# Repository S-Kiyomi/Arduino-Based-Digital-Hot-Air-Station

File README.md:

# 858d HOT AIR REWORK STATION (SVARD858d)

> *sile bace dalam bahase kamek mun kau daan ngerati inggris: [Bahasa Indonesia](/docs/README_ID.md)*

This **ATmega328P** microcontroller-based digital hot-air rework station is an open-source DIY project designed to deliver high(not or maybe)precision temperature control and airflow management. It utilizes a standard 858D hot-air handle, a K-type thermocouple sensor (MAX6675), and a rotary encoder for an intuitive user interface.

In **v2.0**, the firmware has been completely refactored from the standard Arduino core environment to **Pure AVR Bare-Metal C/C++** to achieve overhead-free execution, lightning-fast response times, and an extremely low memory footprint.

> **HIGH VOLTAGE SAFETY WARNING (220V AC)**
> 
> This project deals directly with lethal 220V/230V AC mains electricity. Incorrect assembly can lead to hardware destruction, fire hazard, or fatal electric shock.
> - Never touch any part of the TRIAC/Heater circuitry while the system is connected to mains power.
> - Ensure high-voltage circuits are physically and optocoupled-isolated from microcontroller lines.
> - Assemble and operate entirely at your own risk.
> - DO WITH YOUR OWN RISK
> - MATI TANAM

---

## Key Features

- **Pure Bare-Metal Firmware (v2.0):** Runs without Arduino library dependencies (`Wire.h`, `LiquidCrystal_I2C.h`, `EEPROM.h`, `pinMode`, `digitalWrite`). Compiled natively via `avr-gcc` and `Makefile`.
- **Extreme Memory Footprint Optimization:** Extremely lightweight footprint (~6.4 KB Flash & 128 Bytes SRAM). UI text strings are stored in Flash ROM (`PROGMEM`) with custom lightweight integer formatting.
- **Non-Volatile EEPROM Storage:** Target temperature (`targetTempC`) and fan speed (`fanPercent`) settings are saved automatically to EEPROM upon UI confirmation.
- **PID Control & TRIAC Phase-Angle Timing:** Smoothly heats the element and precisely maintains temperature using AC Zero-Crossing detection (INT0) and Timer2 CTC interrupt timing.
- **Auto-Sleep & Automated Cooldown:** When the handle is placed in its cradle, heater power is instantly cut while the blower fan ramps up to 100% PWM until the nozzle drops below 100°C to prevent thermal damage.
- **Failsafe & Fault Detection:** Instantly cuts power and triggers a *MALFUNCTION* alarm if the thermocouple opens/fails or if the AC Zero-Cross sync pulse is lost.
- **Display Power Management:** LCD backlight automatically turns off after 60 seconds of inactivity.

---

## Component Requirements & Pin Mapping

| Component | Arduino Pin | AVR Port/Pin | Register Type / Function |
| :--- | :--- | :--- | :--- |
| Zero-Cross Signal | D2 | PD2 | External Interrupt 0 (INT0) |
| Encoder SW | D3 | PD3 | Digital Input Pull-up |
| Encoder DT | D4 | PD4 | Digital Input Pull-up |
| Encoder CLK | D5 | PD5 | Digital Input Pull-up |
| Buzzer | D6 | PD6 | Digital Output |
| TRIAC Gate | D7 | PD7 | Digital Output (Timer2 Phase Delay) |
| Handle Switch | D8 | PB0 | Digital Input Pull-up (Sleep/Work) |
| Blower Fan PWM | D9 | PB1 | Output Hardware Fast PWM Timer1 (OC1A) |
| MAX6675 CS | D10 | PB2 | SPI Slave Select (Output) |
| MAX6675 SO | D12 | PB4 | SPI MISO Input |
| MAX6675 SCK | D13 | PB5 | SPI Serial Clock Output |
| LCD 16x2 I2C | A4 / A5 | PC4 / PC5 | Hardware TWI (SDA / SCL) |

---

## Documentation & Firmware Build Guide

For detailed bare-metal architecture, ATmega328P register configuration, and compilation (`make`) and flashing (`avrdude`) instructions, please read the technical documentation:

[Firmware Documentation & Build Guide](firmware/README.md)

---

## License

This project is licensed under the MIT License. You are free to use, modify, and distribute this project for both commercial and non-commercial purposes.

Copyright (c) 2026 Rul Chan & Averyandra. All Rights Reserved.

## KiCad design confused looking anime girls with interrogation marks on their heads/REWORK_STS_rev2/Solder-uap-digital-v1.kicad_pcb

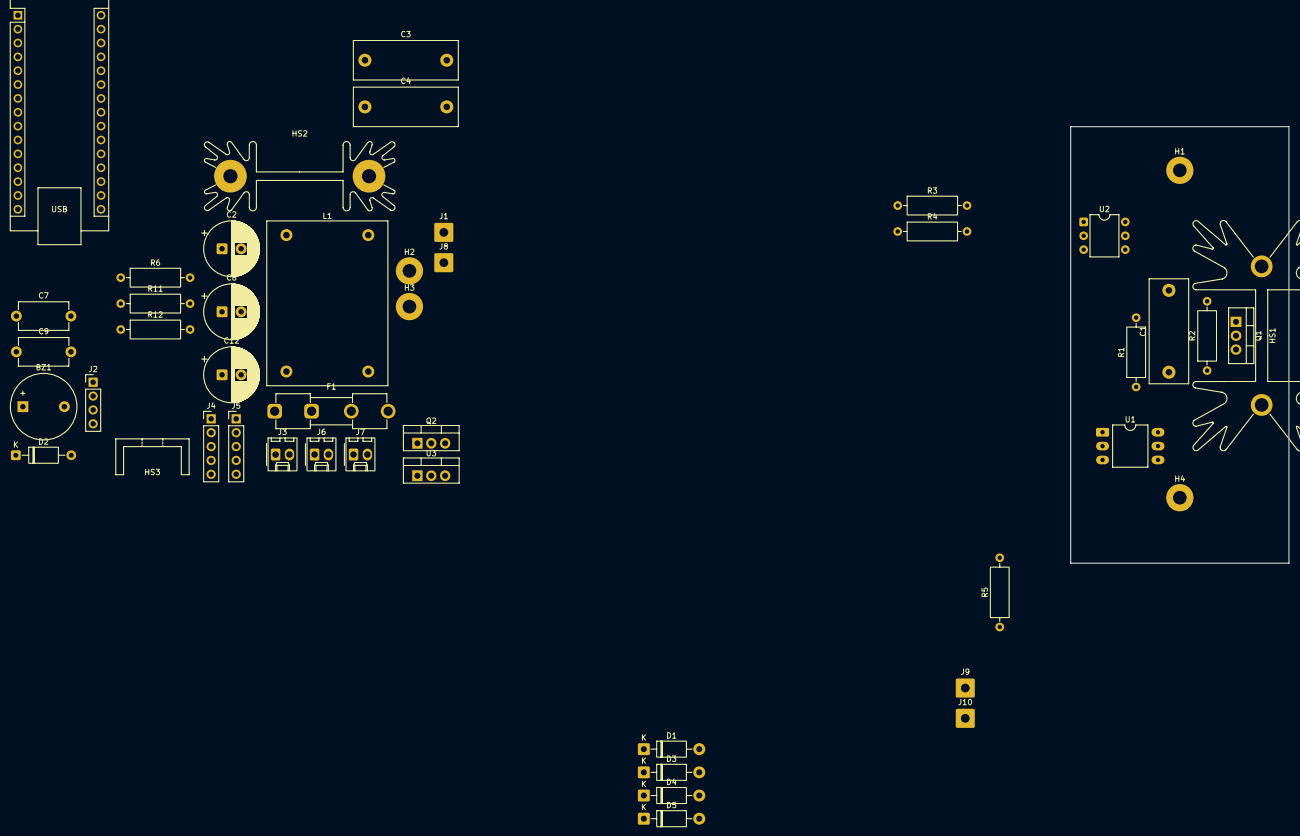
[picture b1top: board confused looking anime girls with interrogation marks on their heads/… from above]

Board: 2 copper layers, 40.0 x 80.0 mm, 47 parts (0 on the bottom side), 33 nets, no tracks yet.

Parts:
A1: Arduino_Nano_v3.x; Arduino_Nano
BZ1: Buzzer; Buzzer_12x9.5RM7.6
C1, C3, C4: 10n; C_Rect_L19.0mm_W7.0mm_P15.00mm_MKS4
C2, C8, C12: 470u; CP_Radial_D10.0mm_P3.50mm
C7, C9: 100n; C_Disc_D9.0mm_W5.0mm_P10.00mm
D1, D3, D4, D5: 1N4007; D_DO-41_SOD81_P10.16mm_Horizontal
D2: HER107; D_A-405_P10.16mm_Horizontal
F1: Fuse; Fuseholder_Clip-5x20mm_Eaton_1A5601-01_Inline_P20.80x6.76mm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
H1, H4: MountingHole; MountingHole_2.5mm_Pad
H2, H3: MountingHole_Pad; MountingHole_2.5mm_Pad
HS1: Heatsink; Heatsink_Fischer_SK129-STS_42x25mm_2xDrill2.5mm
HS2: Heatsink_Pad; Heatsink_AAVID_Extruded_531102B02100G_34.9x12.7mm_H38.1mm
HS3: Heatsink; Heatsink_Stonecold_HS-S01_13.21x6.35mm
J1, J8, J9, J10: Conn_01x01_Pin; SolderWire-0.75sqmm_1x01_D1.25mm_OD3.5mm
J2: LCD-i2c; PinHeader_1x04_P2.54mm_Vertical
J3: FAN_H; Molex_KK-254_AE-6410-02A_1x02_P2.54mm_Vertical
J4: ROTARY_ENCODER_KY-040; PinHeader_1x05_P2.54mm_Vertical
J5: MAX6675; PinHeader_1x05_P2.54mm_Vertical
J6: 24V_IN; Molex_KK-254_AE-6410-02A_1x02_P2.54mm_Vertical
J7: FAN_ENC; Molex_KK-254_AE-6410-02A_1x02_P2.54mm_Vertical
L1: L_Ferrite_Coupled; L_CommonMode_Wuerth_WE-CMB-XL
Q1: BTA16; TO-220-3_Vertical
Q2: TIP41; TO-220-3_Vertical
R1: 470; R_Axial_DIN0309_L9.0mm_D3.2mm_P12.70mm_Horizontal
R2: 39; R_Axial_DIN0309_L9.0mm_D3.2mm_P12.70mm_Horizontal
R3, R4: 27k; R_Axial_DIN0309_L9.0mm_D3.2mm_P12.70mm_Horizontal
R5: 10k; R_Axial_DIN0309_L9.0mm_D3.2mm_P12.70mm_Horizontal
R6: 1k; R_Axial_DIN0309_L9.0mm_D3.2mm_P12.70mm_Horizontal
R11: 330; R_Axial_DIN0309_L9.0mm_D3.2mm_P12.70mm_Horizontal
R12: 100k; R_Axial_DIN0309_L9.0mm_D3.2mm_P12.70mm_Horizontal
U1: MOC3021M; DIP-6_W10.16mm_LongPads
U2: 4N25; DIP-6_W7.62mm
U3: LM7812; TO-220-3_Vertical

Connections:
+5V: J2.2, J4.2, J5.2, R5.1
+12V: A1.30 (VIN), C7.1, C8.1, J7.1, U3.3 (VO)
+24V: C2.1, C12.1, D2.1 (K), J3.2, J6.2, U3.1 (VI)
/FAN-: D2.2 (A), J3.1, Q2.2 (C)
/L: F1.1, J1.1 (Pin_1_1)
/N: C3.2, J8.1 (Pin_1_1)
/OUT_H: C1.2, J10.1 (Pin_1_1), Q1.1 (A1)
/SCL: A1.24 (A5), J2.4
/SDA: A1.23 (A4), J2.3
CLK: A1.8 (D5), J4.5
CS: A1.13 (D10), J5.4
DT: A1.7 (D4), J4.4
FAN_CTRL: A1.12 (D9), R6.1
GND: A1.4 (GND), A1.29 (GND), BZ1.2 (-), C2.2, C7.2, C8.2, C9.1, C12.2, J2.1, J4.1, J5.1, J6.1, J7.2, Q2.3 (E), R12.2, U1.2, U2.4, U3.2 (GND)
GNDPWR: C9.2, H2.1 (1_1), H3.1 (1_1)
LINE: C4.1, D1.1 (K), D3.2 (A), Q1.2 (A2), R1.2, R2.2
NEUTRAL: C4.2, D4.1 (K), D5.2 (A), J9.1 (Pin_1_1)
unnamed: A1.9 (D6), BZ1.1 (+)
unnamed: A1.10 (D7), R11.1
unnamed: C1.1, R2.1
unnamed: C3.1, F1.2, L1.1 (1_1)
unnamed: D1.2 (A), D4.2 (A), R3.2
unnamed: D3.1 (K), D5.1 (K), R4.2
unnamed: Q1.3 (G), U1.4
unnamed: Q2.1 (B), R6.2, R12.1
unnamed: R1.1, U1.6
unnamed: R3.1, U2.2
unnamed: R4.1, U2.1
SCK: A1.16 (D13), J5.3
SIG_TRIAC: R11.2, U1.1
SO: A1.15 (D12), J5.5
SW: A1.6 (D3), J4.3
ZERO_C_D: A1.5 (D2), R5.2, U2.5

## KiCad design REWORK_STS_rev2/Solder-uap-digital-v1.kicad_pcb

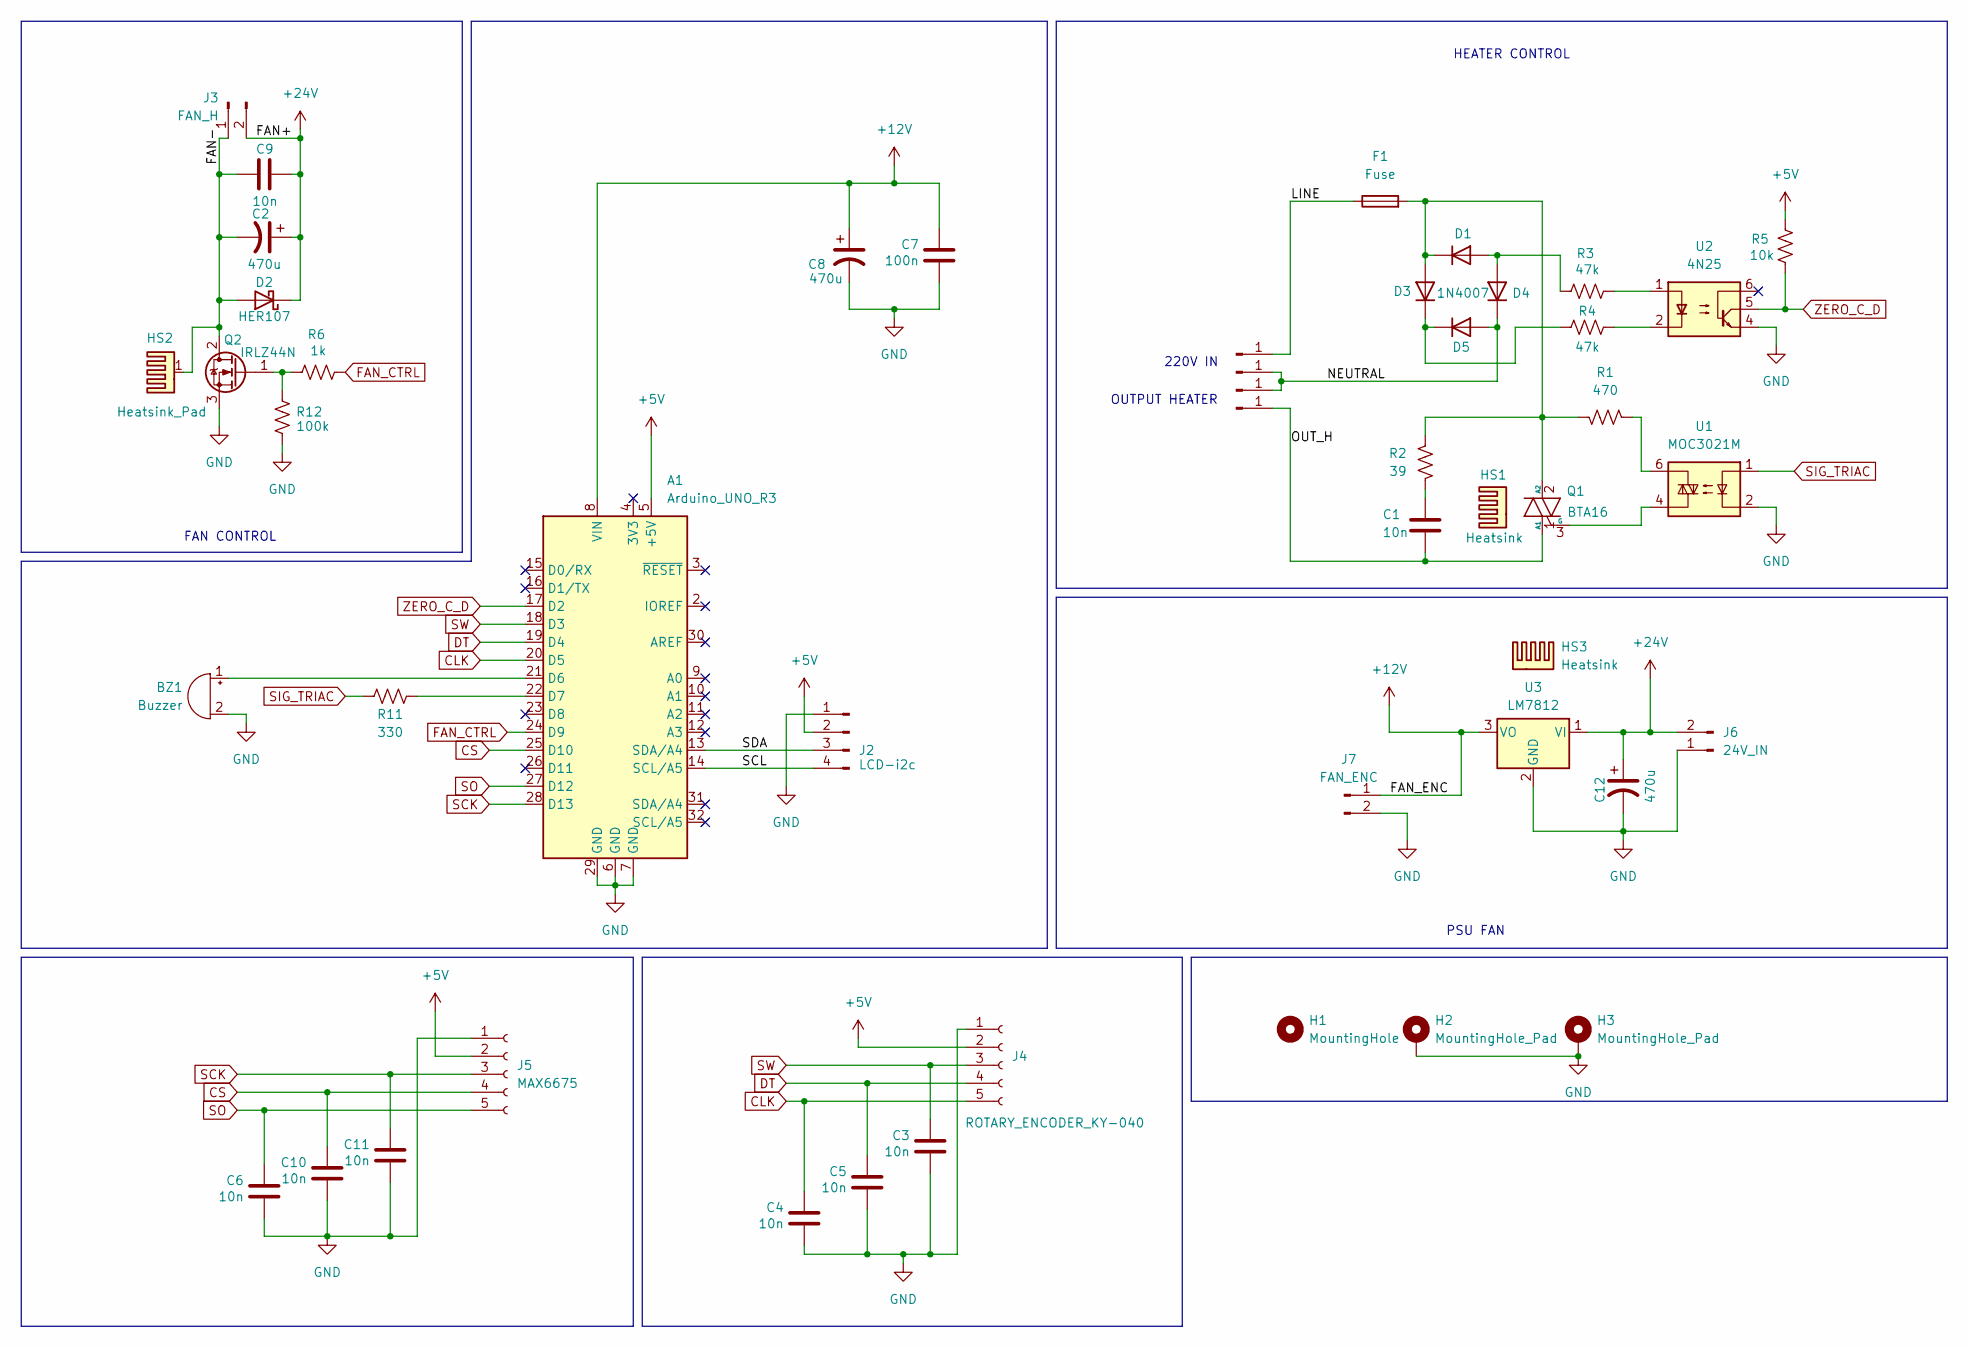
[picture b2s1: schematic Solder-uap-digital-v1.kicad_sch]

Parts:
A1: Arduino_UNO_R3
BZ1: Buzzer; Buzzer_12x9.5RM7.6
C1: 10n; C_Rect_L19.0mm_W7.0mm_P15.00mm_MKS4
C2, C8, C12: 470u; CP_Radial_D10.0mm_P3.50mm
C3, C4, C5, C6, C9, C10, C11: 10n; C_Disc_D9.0mm_W5.0mm_P10.00mm
C7: 100n; C_Disc_D9.0mm_W5.0mm_P10.00mm
D1, D3, D4, D5: 1N4007; D_DO-41_SOD81_P10.16mm_Horizontal
D2: HER107; D_A-405_P10.16mm_Horizontal
F1: Fuse; Fuseholder_Clip-5x20mm_Eaton_1A5601-01_Inline_P20.80x6.76mm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
H1: MountingHole; MountingHole_2.5mm_Pad
H2, H3: MountingHole_Pad; MountingHole_2.5mm_Pad
HS1: Heatsink; Heatsink_Fischer_SK129-STS_42x25mm_2xDrill2.5mm
HS2: Heatsink_Pad; Heatsink_AAVID_Extruded_531102B02100G_34.9x12.7mm_H38.1mm
HS3: Heatsink; Heatsink_Stonecold_HS-S01_13.21x6.35mm
J1, J8, J9, J10: Conn_01x01_Pin; SolderWire-0.75sqmm_1x01_D1.25mm_OD3.5mm
J2: LCD-i2c; PinHeader_1x04_P2.54mm_Vertical
J3: FAN_H; Molex_KK-254_AE-6410-02A_1x02_P2.54mm_Vertical
J4: ROTARY_ENCODER_KY-040; PinHeader_1x05_P2.54mm_Vertical
J5: MAX6675; PinHeader_1x05_P2.54mm_Vertical
J6: 24V_IN; Molex_KK-254_AE-6410-02A_1x02_P2.54mm_Vertical
J7: FAN_ENC; Molex_KK-254_AE-6410-02A_1x02_P2.54mm_Vertical
Q1: BTA16; TO-220-3_Vertical
Q2: IRLZ44N; TO-220-3_Vertical
R1: 470; R_Axial_DIN0309_L9.0mm_D3.2mm_P12.70mm_Horizontal
R2: 39; R_Axial_DIN0309_L9.0mm_D3.2mm_P12.70mm_Horizontal
R3, R4: 47k; R_Axial_DIN0309_L9.0mm_D3.2mm_P12.70mm_Horizontal
R5: 10k; R_Axial_DIN0309_L9.0mm_D3.2mm_P12.70mm_Horizontal
R6: 1k; R_Axial_DIN0309_L9.0mm_D3.2mm_P12.70mm_Horizontal
R11: 330; R_Axial_DIN0309_L9.0mm_D3.2mm_P12.70mm_Horizontal
R12: 100k; R_Axial_DIN0309_L9.0mm_D3.2mm_P12.70mm_Horizontal
U1: MOC3021M; DIP-6_W10.16mm_LongPads
U2: 4N25; DIP-6_W7.62mm
U3: LM7812; TO-220-3_Vertical

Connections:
+5V: A1.5 (+5V), J2.2, J4.2, J5.2, R5.1
+12V: A1.8 (VIN), C7.1, C8.1, J7.1, U3.3 (VO)
+24V: C2.1, C9.2, C12.1, D2.1 (K), J3.2, J6.2, U3.1 (VI)
/FAN-: C2.2, C9.1, D2.2 (A), HS2.1, J3.1, Q2.2 (D)
/LINE: F1.1, J1.1 (Pin_1_1)
/NEUTRAL: D4.1 (K), D5.2 (A), J8.1 (Pin_1_1), J9.1 (Pin_1_1)
/OUT_H: C1.2, J10.1 (Pin_1_1), Q1.1 (A1)
/SCL: A1.14 (SCL/A5), J2.4
/SDA: A1.13 (SDA/A4), J2.3
CLK: A1.20 (D5), C4.1, J4.5
CS: A1.25 (D10), C10.1, J5.4
DT: A1.19 (D4), C5.1, J4.4
FAN_CTRL: A1.24 (D9), R6.1
GND: A1.6 (GND), A1.7 (GND), A1.29 (GND), BZ1.2 (-), C3.2, C4.2, C5.2, C6.2, C7.2, C8.2, C10.2, C11.2, C12.2, H2.1 (1_1), H3.1 (1_1), J2.1, J4.1, J5.1, J6.1, J7.2, Q2.3 (S), R12.2, U1.2, U2.4, U3.2 (GND)
unnamed: A1.21 (D6), BZ1.1 (+)
unnamed: A1.22 (D7), R11.1
unnamed: C1.1, R2.1
unnamed: D1.2 (A), D4.2 (A), R3.2
unnamed: D1.1 (K), D3.2 (A), F1.2, Q1.2 (A2), R1.2, R2.2
unnamed: D3.1 (K), D5.1 (K), R4.2
unnamed: Q1.3 (G), U1.4
unnamed: Q2.1 (G), R6.2, R12.1
unnamed: R1.1, U1.6
unnamed: R3.1, U2.1
unnamed: R4.1, U2.2
SCK: A1.28 (D13), C11.1, J5.3
SIG_TRIAC: R11.2, U1.1
SO: A1.27 (D12), C6.1, J5.5
SW: A1.18 (D3), C3.1, J4.3
ZERO_C_D: A1.17 (D2), R5.2, U2.5

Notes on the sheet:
FAN CONTROL
HEATER CONTROL
PSU FAN
220V IN
OUTPUT HEATER

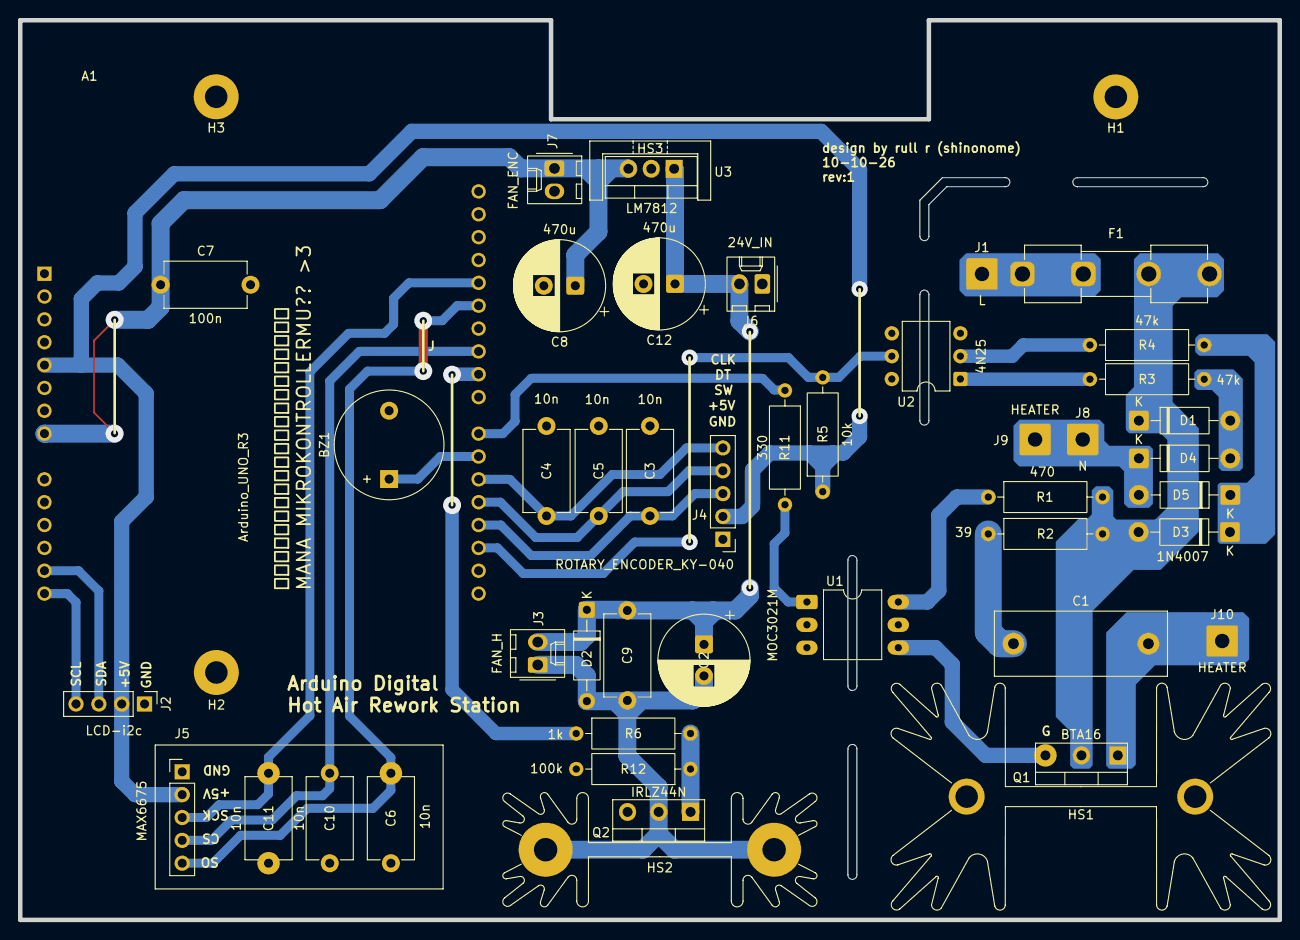
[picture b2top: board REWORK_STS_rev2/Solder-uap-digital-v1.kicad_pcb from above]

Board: 2 copper layers, 140.0 x 100.0 mm, 49 parts (1 on the bottom side), 30 nets.

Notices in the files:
README.md:
License: MIT
